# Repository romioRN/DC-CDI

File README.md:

ВНИМАНИЕ! в плате есть отсутствующие дjрожки если вы хотите это изготовить вам нужно внести исправления

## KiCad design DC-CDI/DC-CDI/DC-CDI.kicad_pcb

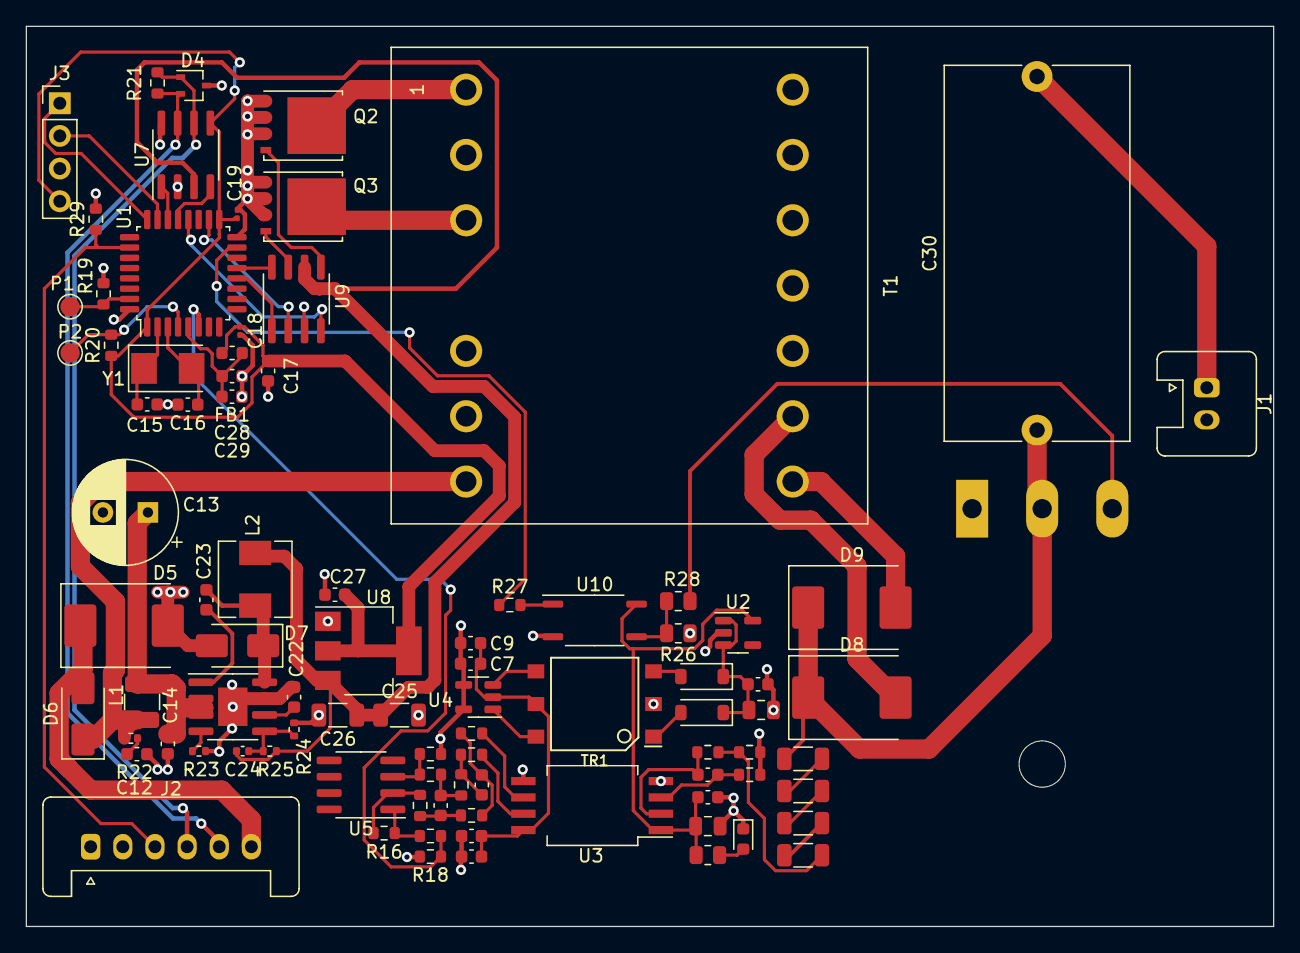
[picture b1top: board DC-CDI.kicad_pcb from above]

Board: 2 copper layers, 97.0 x 70.0 mm, 90 parts (1 on the bottom side), 65 nets.

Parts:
C1, C3: 10u; C_0805_2012Metric
C2, C4, C6, C7, C23: 100n; C_0603_1608Metric
C5: 330p; C_0603_1608Metric
C8: 2.2u; C_0603_1608Metric
C9: 10u; C_0603_1608Metric
C10: 2.2n; C_0603_1608Metric
C11: 220p; C_0603_1608Metric
C12, C17, C27: 4.7u; C_0603_1608Metric
C13: 56u; CP_Radial_D8.0mm_P3.50mm
C14: 1u; C_0603_1608Metric
C15, C16: 18pF; C_0603_1608Metric
C18, C19: 100n; C_0201_0603Metric
C22: 10n; C_0603_1608Metric
C24: 330p; C_0402_1005Metric
C25, C26: 10u; C_1206_3216Metric
C28: 4.7uF; C_0603_1608Metric
C29: 100nF; C_0603_1608Metric
C30: 5u; C_Rect_L29.0mm_W14.2mm_P27.50mm_MKT
D1: POWER; LED_0603_1608Metric
D2, D3: MBR0520; D_SOD-123
D4: PESD1CAN-UX; SOT-323_SC-70
D5: SM15T33CA; D_SMC
D6, D7: D_Schottky; D_SMA
D8, D9: ES3J; D_SMC
FB1: FerriteBead; L_0603_1608Metric
J1: Conn_01x02; Stocko_MKS_1652-6-0-202_1x2_P2.50mm_Vertical
J2: Conn_01x06; Stocko_MKS_1656-6-0-606_1x6_P2.50mm_Vertical
J3: Conn_01x04; PinHeader_1x04_P2.54mm_Vertical
L1: 2.2u; L_1210_3225Metric
L2: 10u; L_Sunlord_MWSA0503S
P1, P2: Pad; TestPoint_Pad_D1.5mm
Q1: TIC106; TO-247-3_Horizontal_TabDown
Q2, Q3: BSC026N08NS5; TDSON-8-1
R1: 470; R_0805_2012Metric
R2, R3, R4, R5: 470K; R_1206_3216Metric
R6, R7, R11, R12: 1k; R_0603_1608Metric
R8: 10; R_0603_1608Metric
R9, R10: 100; R_0603_1608Metric
R13, R14: 5.6k; R_0603_1608Metric
R15, R16: 33K; R_0603_1608Metric
R17: 10k; R_0603_1608Metric
R18: 3.3k; R_0603_1608Metric
R19, R20, R27, R29: 10K; R_0603_1608Metric
R21: 120; R_0603_1608Metric
R22: 1; R_0402_1005Metric
R23: 10k; R_0402_1005Metric
R24: 12k; R_0402_1005Metric
R25: 68k; R_0402_1005Metric
R26, R28: 4.7к; R_0805_2012Metric
T1: Transformer_EPCOS_B66359A1013T_Horizontal
TR1: TRANSF5; WURTH-760390014
U1: STM32F334K8Tx; LQFP-32_7x7mm_P0.8mm
U2: TPS76350; SOT-23-5
U3: AMC1301; SSO-8_6.8x5.9mm_P1.27mm_Clearance8mm
U4: SN6501DBV; SOT-23-5
U5: OPA2197IDR; SOIC-8_3.9x4.9mm_P1.27mm
U6: LMR14020; SOIC-8-1EP_3.9x4.9mm_P1.27mm_EP2.29x3mm
U7: TJA1051T-3; SOIC-8_3.9x4.9mm_P1.27mm
U8: AMS1117-3.3; SOT-223-3_TabPin2
U9: FAN3223; SOIC-8_3.9x4.9mm_P1.27mm
U10: TLP185; SOIC-4_4.55x3.7mm_P2.54mm
Y1: 8MHz; Crystal_SMD_5032-2Pin_5.0x3.2mm

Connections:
+3.3V: C17.2, C18.2, C19.2, C27.1, FB1.2, J3.4, R20.1, U1.1 (VDD), U1.17 (VDD), U7.5 (VIO), U8.2 (VO)
+3V3: C6.1, C7.1, C8.1, C9.1, TR1.5, U3.8 (VDD2), U4.2 (VCC)
+5V: C24.1, C25.1, C26.1, L2.2, R25.2, U7.3 (VCC), U8.3 (VI), U9.6 (VDD)
+12V: D6.1 (K), L1.1, R22.1, T1.7
/12V_RAW: D5.1 (A1), D6.2 (A), J2.6
/Boot0: P1.1, R19.1, U1.31 (BOOT0)
/CANH: D4.2 (A2), J2.5, R21.1, U7.7 (CANH)
/CANL: D4.1 (A1), J2.4, R21.2, U7.6 (CANL)
/ENA: U1.12 (PA6), U9.1 (ENA)
/ENB: U1.13 (PA7), U9.8 (ENB)
/HV: R17.2, R18.1, U1.6 (PA0)
/HV_OUT: C30.1, D8.1 (K), D9.1 (K), Q1.2 (A), R2.1
/IGN_IN: J2.3, R29.1, U1.26 (PB3)
/IN_OUT: R27.1, U1.15 (PB1)
/ISO+5V: C1.1, C4.1, R1.2, U2.5 (VOUT), U3.1 (VDD1), U10.6
/RXDCAN: U1.21 (PA11), U7.4 (RXD)
/SWCLK: J3.1, U1.24 (PA14)
/SWDIO: J3.2, U1.23 (PA13)
/TXDCAN: U1.22 (PA12), U7.1 (TXD)
GND: C6.2, C7.2, C8.2, C9.2, C12.2, C13.2, C14.2, C15.2, C16.2, C17.1, C18.1, C19.1, C22.2, C25.2, C26.2, C27.2, C28.2, C29.1, D4.3 (common), D5.2 (A2), D7.2 (A), J2.1, J3.3, Q2.1 (S), Q2.2 (S), Q2.3 (S), Q3.1 (S), Q3.2 (S), Q3.3 (S), R15.2, R18.2, R19.2, R23.2, R24.2, R29.2, U1.16 (VSS), U1.32 (VSS), U3.5 (GND2), U4.4 (GND), U4.5 (GND), U6.7 (GND), U6.9 (GND), U7.2 (GND), U7.8 (S), U8.1 (GND), U9.3 (GND), U10.3
GNDA: C1.2, C2.2, C3.2, C4.2, D1.1 (K), J1.2, Q1.1 (K), R6.2, R7.2, R26.1, T1.10, T1.11, TR1.2, U2.2 (GND), U3.4 (GND2)
unnamed: C10.1, R9.1, R11.1
unnamed: C10.2, R10.1, R12.1
unnamed: C11.1, R11.2, R13.1
unnamed: C11.2, R12.2, R14.1
unnamed: C12.1, R22.2
unnamed: D1.2 (A), R1.1
unnamed: D2.2 (A), TR1.1
unnamed: C2.1, C3.1, D2.1 (K), D3.1 (K), U2.1 (VIN), U2.3 (EN)
unnamed: D3.2 (A), TR1.3
unnamed: C23.2, D7.1 (K), L2.1, U6.8 (SW)
unnamed: D8.2 (A), T1.9
unnamed: D9.2 (A), T1.8
unnamed: C30.2, J1.1
unnamed: P2.1, R20.2, U1.4 (NRST)
unnamed: Q1.3 (G), R28.1
unnamed: Q2.5 (D), T1.1
unnamed: Q2.4 (G), U9.5 (~OUTB)
unnamed: Q3.5 (D), T1.3
unnamed: Q3.4 (G), U9.7 (OUTA)
unnamed: R2.2, R3.1
unnamed: R3.2, R4.1
unnamed: R4.2, R5.1
unnamed: R5.2, R6.1, R8.1
unnamed: R16.2, R17.1, U5.1
unnamed: R26.2, R28.2, U10.4
unnamed: R27.2, U10.1
unnamed: U1.18 (PA8), U9.2 (INA)
unnamed: U1.20 (PA10), U9.4 (INB)
unnamed: C15.1, U1.2 (PF0), Y1.1
unnamed: C16.1, U1.3 (PF1), Y1.2
unnamed: C28.1, C29.2, FB1.1, U1.5 (VDDA)
unnamed: C5.2, R7.1, U3.3 (VINN)
unnamed: C5.1, R8.2, U3.2 (VINP)
unnamed: R9.2, U3.6 (VOUTN)
unnamed: R10.2, U3.7 (VOUTP)
unnamed: TR1.6, U4.1 (D1)
unnamed: TR1.4, U4.3 (D2)
unnamed: R14.2, R15.1, U5.3 (+)
unnamed: R13.2, R16.1, U5.2 (-)
unnamed: C23.1, U6.1 (BOOT)
unnamed: C13.1, C14.1, L1.2, U6.2 (VIN), U6.3 (EN)
unnamed: C24.2, R24.1, R25.1, U6.5 (FB)
unnamed: R23.1, U6.4 (RT)
unnamed: C22.1, U6.6 (SS)
